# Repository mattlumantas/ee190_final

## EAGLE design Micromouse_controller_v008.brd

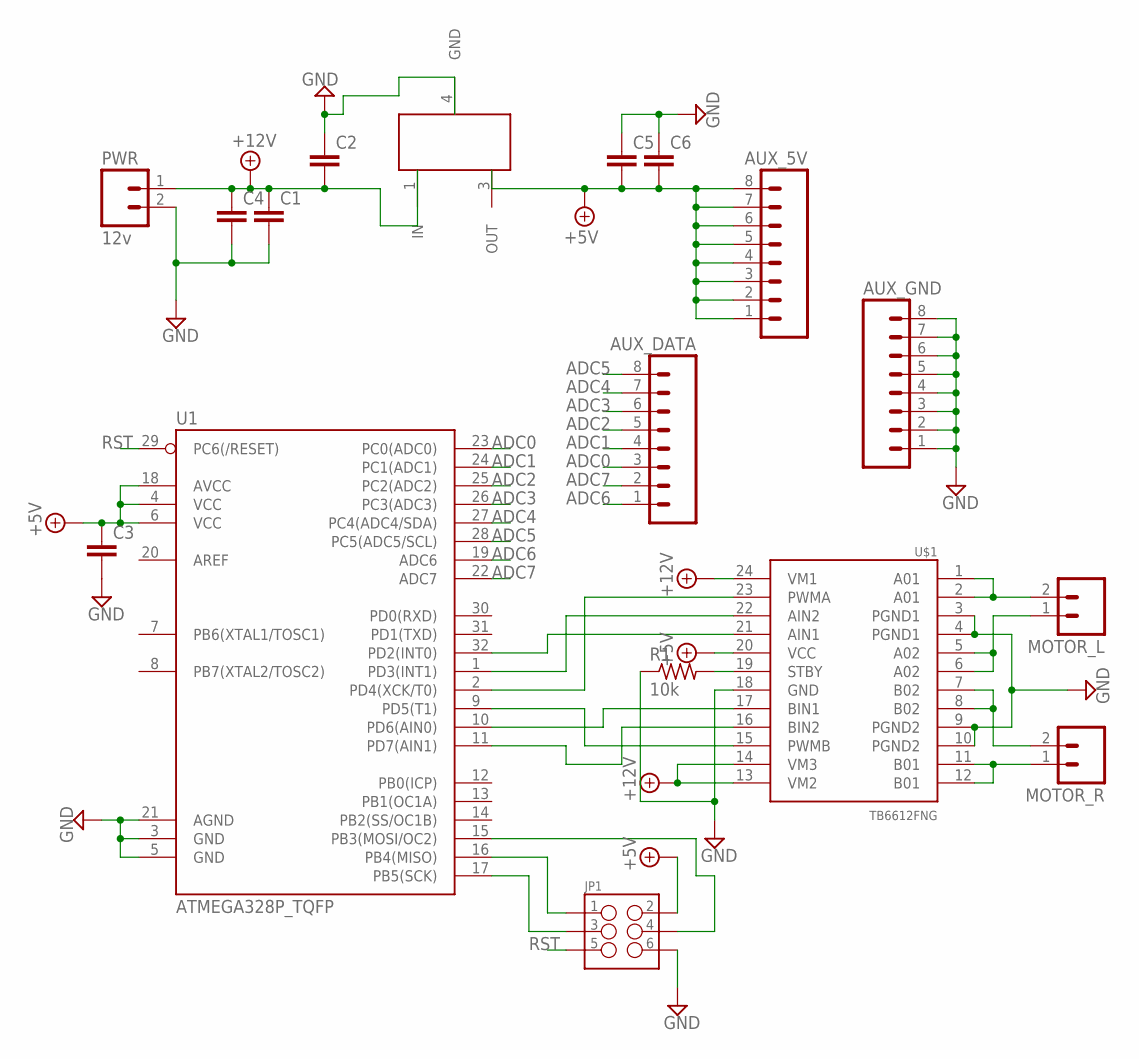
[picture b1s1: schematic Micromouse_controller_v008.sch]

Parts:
AUX_5V: M08SMD-STRAIGHT-ALT-FEMALE; 1X08_SMD_ALT
AUX_DATA: M08SMD-STRAIGHT-ALT-FEMALE; 1X08_SMD_ALT
AUX_GND: M08SMD-STRAIGHT-ALT-FEMALE; 1X08_SMD_ALT
C1, C2, C3, C4, C5, C6: CAPSMD; GRM43D
IC2: TA4805BF; DPAK
JP1: M03X2FEMALE_SMD; 2X3_SMD
MOTOR_L: M02-JST-2MM-SMT; JST-2-SMD
MOTOR_R: M02-JST-2MM-SMT; JST-2-SMD
PWR: 12v; JST-2-SMD
R1: 10k; R0603
U1: ATMEGA328P_TQFP; TQFP32-08
U$1: TB6612FNG; SSOP24

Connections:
+5V: AUX_5V.1, AUX_5V.2, AUX_5V.3, AUX_5V.4, AUX_5V.5, AUX_5V.6, AUX_5V.7, AUX_5V.8, C3.A (1), C5.C (2), C6.C (2), IC2.3 (OUT), JP1.2, U1.4 (VCC), U1.6 (VCC), U1.18 (AVCC), U$1.20 (VCC)
+12V: C1.A (1), C2.C (2), C4.A (1), IC2.1 (IN), PWR.1 (2), U$1.13 (VM2), U$1.14 (VM3), U$1.24 (VM1)
ADC0: AUX_DATA.3, U1.23 (PC0(ADC0))
ADC1: AUX_DATA.4, U1.24 (PC1(ADC1))
ADC2: AUX_DATA.5, U1.25 (PC2(ADC2))
ADC3: AUX_DATA.6, U1.26 (PC3(ADC3))
ADC4: AUX_DATA.7, U1.27 (PC4(ADC4/SDA))
ADC5: AUX_DATA.8, U1.28 (PC5(ADC5/SCL))
ADC6: AUX_DATA.1, U1.19 (ADC6)
ADC7: AUX_DATA.2, U1.22 (ADC7)
AIN1_DRIVER: U1.32 (PD2(INT0)), U$1.21 (AIN1)
AIN2_DRIVER: U1.1 (PD3(INT1)), U$1.22 (AIN2)
BIN1_DRIVER: U1.10 (PD6(AIN0)), U$1.17 (BIN1)
BIN2_DRIVER: U1.11 (PD7(AIN1)), U$1.16 (BIN2)
GND: AUX_GND.1, AUX_GND.2, AUX_GND.3, AUX_GND.4, AUX_GND.5, AUX_GND.6, AUX_GND.7, AUX_GND.8, C1.C (2), C2.A (1), C3.C (2), C4.C (2), C5.A (1), C6.A (1), IC2.4 (GND), JP1.6, PWR.2 (1), R1.1, U1.3 (GND), U1.5 (GND), U1.21 (AGND), U$1.3 (PGND1), U$1.4 (PGND1), U$1.9 (PGND2), U$1.10 (PGND2), U$1.18 (GND)
unnamed: MOTOR_L.2 (1), U$1.1 (A01), U$1.2 (A01)
unnamed: MOTOR_L.1 (2), U$1.5 (A02), U$1.6 (A02)
unnamed: MOTOR_R.1 (2), U$1.11 (B01), U$1.12 (B01)
unnamed: MOTOR_R.2 (1), U$1.7 (B02), U$1.8 (B02)
unnamed: JP1.1, U1.16 (PB4(MISO))
unnamed: JP1.3, U1.17 (PB5(SCK))
unnamed: JP1.4, U1.15 (PB3(MOSI/OC2))
PWMA_DRIVER: U1.2 (PD4(XCK/T0)), U$1.23 (PWMA)
PWMB_DRIVER: U1.9 (PD5(T1)), U$1.15 (PWMB)
RST: JP1.5, U1.29 (PC6(/RESET))
STBY: R1.2, U$1.19 (STBY)

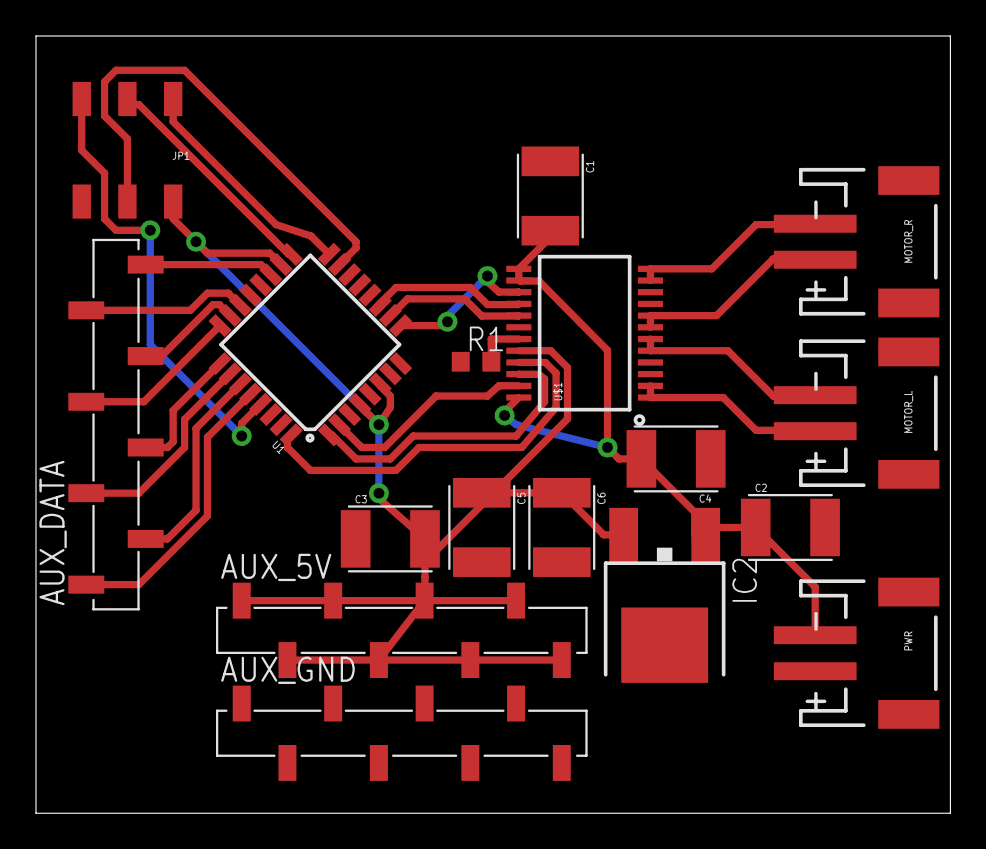
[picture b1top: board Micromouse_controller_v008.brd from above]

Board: 2 copper layers, 50.8 x 43.2 mm, 17 parts (0 on the bottom side), 26 nets.

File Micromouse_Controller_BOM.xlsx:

Quantity | Schematic Label | Item | Package | Vendor | Part # | Price | Quantity Price | Description
1 | U1 | ATmega328P | 32-TQFP | Digikey | ATMEGA328P-AURDKR-ND | 3.7 | 3.7 | Microcontroller
1 | U$1 | TB6612FNG | 24-SSOP | Digikey | TB6612FNGC8ELCT-ND | 1.75 | 1.75 | Motor Driver
1 | IC2 | TA4805BF | DPAK | Digikey | TA4805BF(T6L1NQ)CT-ND | 0.9 | 0.9 | Linear Voltage Regulator (5V)
3 | PWR, MOTOR_L, MOTOR_R | 2-Pin Header | N/A | Sparkfun | PRT-08612 | 0.95 | 2.85 | JST Right Angle Connector - White
3 | AUX_DATA, AUX_5V, AUX_GND | 8-Pin Header | N/A | Digikey | ED4108-ND | 2.8 | 8.4 | Mill-Max 8-Pin Female Connector
1 | PRGRMR | 6-Pin Header | N/A | Digikey | S6010-03-ND | 1.12 | 1.12 | ISP Header
2 | C4, C5 | 0.1uF Capacitor | 1812 (4532 Metric) | Digikey | 490-3518-1-ND | 0.86 | 1.72 | 0.1uF Ceramic Capacitor
2 | C2, C3 | 1uF Capacitor | 1812 (4532 Metric) | Digikey | 445-6108-1-ND | 0.83 | 1.66 | 1uF Ceramic Capacitor
2 | C1, C6 | 10uF Capacitor | 1812 (4532 Metric) | Digikey | 445-1445-1-ND | 1.27 | 2.54 | 10uF Ceramic Capacitor
 |  |  |  |  |  | Total Price: | 24.64

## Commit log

2015-05-28 Added programmer header Pre-pin fiddling Signed-off-by: Matthew Lumantas <mluma001@ucr.edu>
2015-05-28 Added decoupling capacitors Reorganized pins for ease of routing Routed board Signed-off-by: Matthew Lumantas <mluma001@ucr.edu>
2015-05-28 Forgot to connect capacitor C4 to ground
    Todo:
    Calculate/Add values to capacitors
    Fix Design rules routing
2015-05-28 Fixed power supply to TB6612FNG VM1 and VCC were not connected to supply Fixed vias Fixed design clearance errors
2015-05-29 Changed size of board and some small schematic cleanup
2015-05-29 Fixed minor warnings, added BOM and PPT
    Minor warnings on schematic reduced, only real problems that persist are
    with the voltage regulator. If we use the one from lab 1 it would fix it
    though. Excel and Powerpoint files added as well.
2015-05-30 Fixed voltage regulator Replaced with custom DPAK-package for: http://www.digikey.com/product-detail/en/TA4805BF%28T6L1,NQ%29/TA4805BF%28T6L1NQ%29CT-ND/2273194
2015-05-30 Changed library of custom voltage regulator for ease of transfer
2015-06-01 Version 1.0 of Micromouse controller Added capacitor values Arranged Labels Completed BoM and Presentation
2015-06-01 Version 1.01 Added Gerber files

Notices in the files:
parts and their libraries:
SparkFun-Connectors: Licensing: Creative Commons ShareAlike 4.0 International - https://creativecommons.org/licenses/by-sa/4.0
